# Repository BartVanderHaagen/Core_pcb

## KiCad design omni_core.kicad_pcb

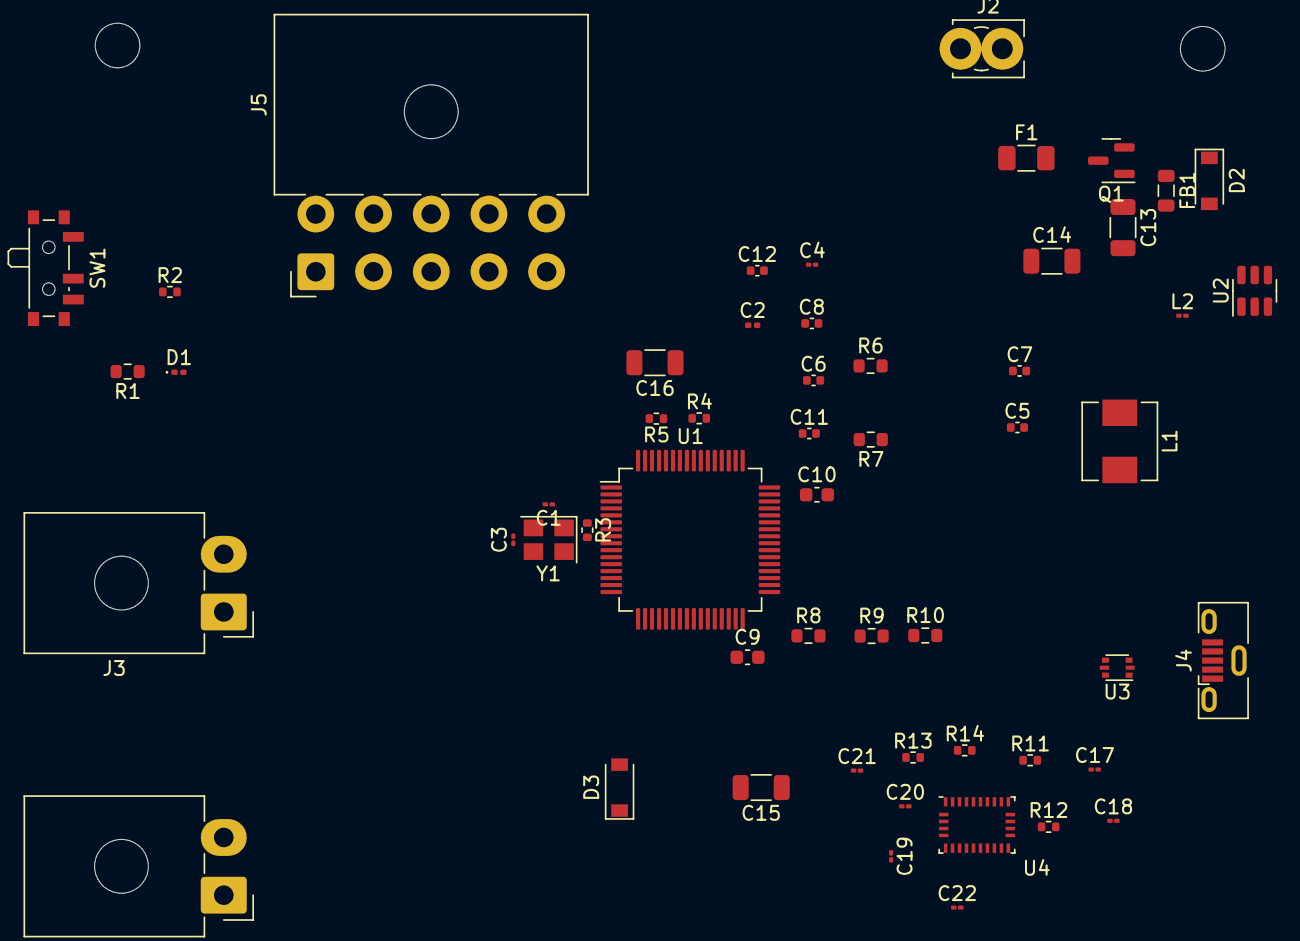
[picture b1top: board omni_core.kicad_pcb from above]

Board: 4 copper layers, 59 parts (0 on the bottom side), 42 nets, no tracks yet.

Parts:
C1, C3: 12p; C_01005_0402Metric
C2: 4u7; C_0201_0603Metric
C4: 100n; C_01005_0402Metric
C5: 1u; C_0402_1005Metric
C6, C8, C11, C12: 100n; C_0402_1005Metric
C7: 10n; C_0402_1005Metric
C9, C10: 2n2; C_0603_1608Metric
C13, C15, C16: 10u; C_1206_3216Metric
C14: 10n; C_1206_3216Metric
C17: 6.8nF; C_01005_0402Metric
C18: 120nF; C_01005_0402Metric
C19, C22: 100nF; C_01005_0402Metric
C20, C21: 22pF; C_01005_0402Metric
D1: Blue; LED_0201_0603Metric
D2, D3: b5819w; D_SOD-123
F1: 250mA; Fuse_1206_3216Metric
FB1: FerriteBead_Small; L_0805_2012Metric
H1, H2, H3, H4: MountingHole_Pad; MountingHole_3.2mm_M3
J1: i2C; TE_MATE-N-LOK_1-770966-x_1x02_P4.14mm_Horizontal
J2: Screw_Terminal_01x02; TerminalBlock_MetzConnect_360273_1x01_Horizontal_ScrewM2.6_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
J3: Uart; TE_MATE-N-LOK_1-770966-x_1x02_P4.14mm_Horizontal
J4: USB_B_Micro; USB_Micro-B_Molex-105133-0001
J5: SWD; TE_MATE-N-LOK_1-770971-x_2x05_P4.14mm_Horizontal
L1: 39h; L_Sunlord_MWSA0518_5.4x5.2mm
L2: 10uh; L_01005_0402Metric
Q1: AO3401A; SOT-23
R1: 1k5; R_0603_1608Metric
R2: 10K; R_0402_1005Metric
R3, R14: 47R; R_0402_1005Metric
R4, R5, R11, R12, R13: 2k2; R_0402_1005Metric
R6: 100k; R_0603_1608Metric
R7: 68k; R_0603_1608Metric
R8: 47k; R_0603_1608Metric
R9: 15; R_0603_1608Metric
R10: 270r; R_0603_1608Metric
SW1: SW_SPDT; SW_SPDT_PCM12
U1: STM32F405RGT6; LQFP-64_10x10mm_P0.5mm
U2: mp2359DJ-LF-Z; SOT-23-6
U3: USBLC6-2P6; SOT-666
U4: BNO055; LGA-28_5.2x3.8mm_P0.5mm
Y1: 16MHz; Crystal_SMD_3225-4Pin_3.2x2.5mm

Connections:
+3.3VA: C5.1, C7.1, L1.2, U1.13 (VDDA)
+3V3: C2.1, C4.1, C6.1, C8.1, C11.1, C12.1, C15.1, C16.1, C19.1, J1.1, J3.1, J5.1, L1.1, L2.2, R4.2, R5.2, R8.1, R11.2, R12.2, SW1.1 (A), U1.1 (VBAT), U1.19 (VDD), U1.32 (VDD), U1.48 (VDD), U1.64 (VDD), U4.3 (VDD)
+5V: D2.2 (A), J4.1 (VBUS), U3.5 (VBUS)
+12V: F1.1, J2.1
BOOT: R2.1, U1.60 (BOOT0)
BUCK_BST: C14.1, U2.1 (BST)
BUCK_FB: R8.2, R9.1, U2.3 (FB)
BUCK_IN: C13.2, FB1.2, R6.1, U2.5 (IN)
BUCK_OUT: R6.2, R7.1, U2.4 (EN)
BUCK_SW: C14.2, D3.1 (K), L2.1, U2.6 (SW)
GND: C1.2, C2.2, C3.2, C4.2, C5.2, C6.2, C7.2, C8.2, C9.2, C10.2, C11.2, C12.2, C13.1, C15.2, C16.2, C19.2, C20.2, C21.2, C22.1, D3.2 (A), J4.5 (GND), J5.3, J5.5, J5.9, Q1.1 (G), R1.2, R7.2, R10.2, SW1.3 (C), U1.12 (VSSA), U1.18 (VSS), U1.63 (VSS), U2.2 (GND), U3.2 (GND), U4.2 (GND), U4.5 (PS1), U4.6 (PS0), Y1.2, Y1.4
GNDIO: C17.1, C18.1, U4.16 (GNDIO), U4.25 (GNDIO)
HSE_in: C1.1, U1.5 (PH0), Y1.1
HSE_out: R3.1, U1.6 (PH1)
LED_STATUS: D1.2 (A), U1.16 (PA2)
unnamed: C3.1, R3.2, Y1.3
unnamed: C9.1, U1.31 (VCAP_1)
unnamed: C10.1, U1.47 (VCAP_2)
unnamed: C21.1, R14.1
unnamed: C22.2, U4.9 (CAP)
unnamed: D1.1 (K), R1.1
unnamed: D2.1 (K), FB1.1, Q1.2 (S)
unnamed: F1.2, Q1.3 (D)
unnamed: R2.2, SW1.2 (B)
unnamed: R9.2, R10.1
unnamed: R13.2, U4.4 (~BOOT_LOAD_PIN)
SWCLK: J5.4, U1.49 (PA14)
SWDIO: J5.2, U1.46 (PA13)
SWO: J5.6, U1.55 (PB3)
UART_TX: J3.2, U1.29 (PB10)
USB D+: U1.45 (PA12), U3.4 (I/O2)
USB D-: U1.44 (PA11), U3.6 (I/O1)
USB_CONN+: J4.3 (D+), U3.3 (I/O2)
USB_CONN-: J4.2 (D-), U3.1 (I/O1)
VDDIO: C17.2, C18.2, R13.1, U4.28 (VDDIO)
Y_IN: R14.2, U4.27 (XIN32)
Y_OUT: C20.1, U4.26 (XOUT32)
i2C1_SCL: J1.2, R4.1, U1.58 (PB6)
i2C1_SDA: R5.1, U1.59 (PB7)
i2C2_SCL: R12.1, U1.61 (PB8), U4.19 (COM1)
i2C2_SDA: R11.1, U1.62 (PB9), U4.20 (COM0)
reset: J5.10, U1.7 (NRST)
